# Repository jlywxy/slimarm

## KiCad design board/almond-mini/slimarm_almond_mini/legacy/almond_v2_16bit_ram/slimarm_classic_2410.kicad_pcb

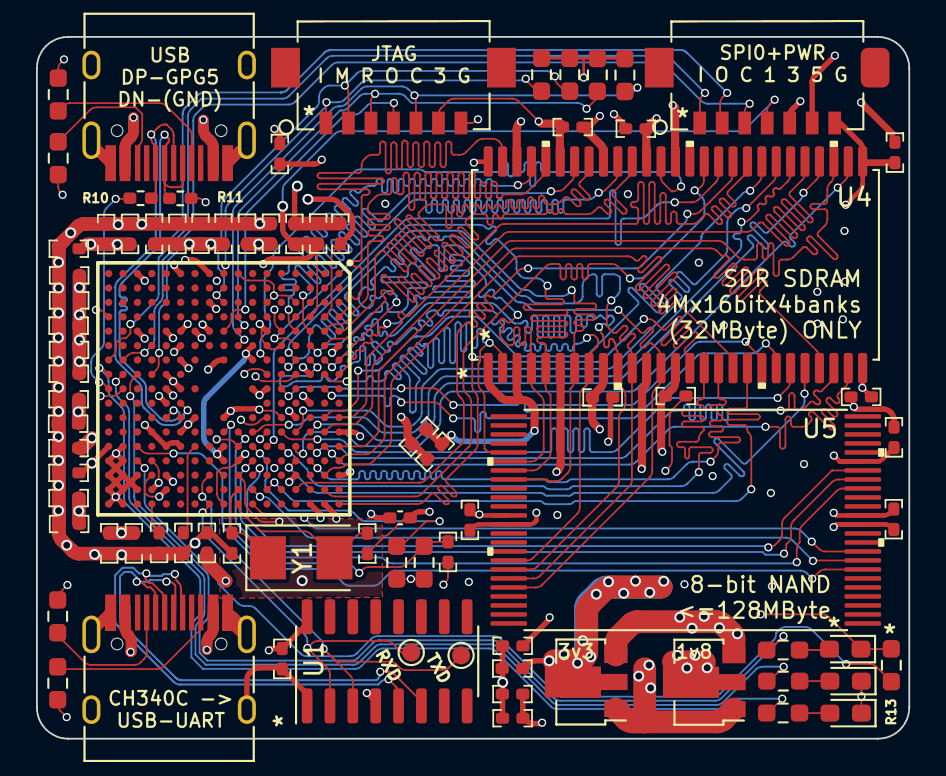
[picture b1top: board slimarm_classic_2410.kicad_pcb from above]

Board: 4 copper layers, 48.5 x 39.0 mm, 81 parts (0 on the bottom side), 81 nets.

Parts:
C1, C2: 5pF; 0402
C3, C4, C5, C7, C8, C11, C13, C14, C15, C16, C17, C18, C19, C20, C21, C22, C23, C24, C25, C26, C27, C28, C30, C31, C32, C33, C34, C35, C36, C37, C38, C39, C40, C41, C42, C43, C44, C45, C46, C47, C48, C49, C50, C51: 100nF; 0402
C6, C12: 22pF; 0402
C29: 100nF; C_0402_1005Metric_Pad0.74x0.62mm_HandSolder
D1, D2, D3: LED; LED_0603_1608Metric_Pad1.05x0.95mm_HandSolder
IC1: S3C2410AXX-YO; BGA272C80P17X17_1400X1400X116
J1, J4: USB_C_Receptacle_USB2.0; USB_C_Receptacle_HRO_TYPE-C-31-M-12
J2, J3: DF13A-7P-1.25H21
R1: 1.5k; R_0603_1608Metric_Pad0.98x0.95mm_HandSolder
R2, R14, R15, R16, R17: 10k; R_0603_1608Metric_Pad0.98x0.95mm_HandSolder
R4, R5, R6: 5.6k; R_0603_1608Metric_Pad0.98x0.95mm_HandSolder
R7, R8, R9, R12: 5.1k; R_0603_1608Metric_Pad0.98x0.95mm_HandSolder
R10, R11: NC; R_0402_1005Metric_Pad0.72x0.64mm_HandSolder
R13: 0; R_0603_1608Metric_Pad0.98x0.95mm_HandSolder
RXD: TestPoint; TestPoint_Pad_D1.0mm
TXD: TestPoint; TestPoint_Pad_D1.0mm
U1: CH340C; SOIC-16_3.9x9.9mm_P1.27mm
U4: HY57V561620FTP
U5: K9F5608U0C; M29W640FB70N6E
U6: AMS1117; SOT-89-3
U7: AMS1117-1.8; SOT-89-3
Y1: 12MHz; Crystal_SMD_5032-2Pin_5.0x3.2mm

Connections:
+1V8: C33.2, C34.2, C35.2, C36.2, C37.2, C38.2, C39.2, C40.2, C41.2, C42.2, C43.2, C44.2, C45.2, C46.2, C47.2, C49.2, IC1.C4 (VDDI_1), IC1.C8 (VDDI_2), IC1.C17 (VDDI_3), IC1.D11 (VDDI_4), IC1.G6 (VDDALIVE_1), IC1.G7 (VDDIARM_1), IC1.J13 (VDDI_5), IC1.J14 (VDDALIVE_2), IC1.K3 (VDDIARM_2), IC1.L5 (VDDIARM_3), IC1.L11 (VDDI_UPLL), IC1.M7 (VDDIARM_4), IC1.M12 (RTCVDD), IC1.N5 (VDDIARM_5), IC1.N10 (VDDIARM_6), IC1.P14 (VDDI_MPLL), IC1.P16 (XTIRTC), IC1.R1 (VDDIARM_7), J2.4, U7.2 (VO)
+3V3: C3.2, C4.2, C5.2, C7.2, C8.2, C11.2, C13.2, C14.2, C15.2, C16.2, C18.2, C19.2, C20.2, C21.2, C22.2, C23.2, C24.2, C25.2, C26.2, C27.2, C28.2, C29.2, C30.2, C31.2, C32.2, C50.2, IC1.A6 (VDDMOP_1), IC1.A15 (VDDMOP_2), IC1.B4 (VDDMOP_3), IC1.D8 (VDDMOP_4), IC1.E5 (VDDMOP_5), IC1.E11 (VDDMOP_6), IC1.H14 (VDDMOP_7), IC1.J11 (EXTCLK), IC1.J17 (NBATT_FLT), IC1.K1 (VDDOP_1), IC1.M6 (VDDOP_2), IC1.N9 (VDDOP_3), IC1.N16 (VDDOP_4), IC1.P15 (VDDA_ADC), IC1.U13 (NCON), J2.5, J3.6, R1.1, R2.2, R14.1, R15.1, R16.1, R17.1, U1.4 (V3), U1.16 (VCC), U4.1 (VDD), U4.3 (VDDQ), U4.9 (VDDQ), U4.14 (VDD), U4.27 (VDD), U4.43 (VDDQ), U4.49 (VDDQ), U5.12 (VCC), U5.19 (WP#), U5.37 (VCC), U6.2 (VO)
+5V: C17.2, C48.2, J1.A4 (VBUS), J1.A9 (VBUS), J1.B4 (VBUS), J1.B9 (VBUS), J2.6, J4.A4 (VBUS), J4.A9 (VBUS), J4.B4 (VBUS), J4.B9 (VBUS), U6.3 (VI), U7.3 (VI)
/BUS_ADR1: IC1.D14 (ADDR1), U4.23 (A0)
/BUS_ADR2: IC1.A14 (ADDR2), U4.24 (A1)
/BUS_ADR3: IC1.C13 (ADDR3), U4.25 (A2)
/BUS_ADR4: IC1.B13 (ADDR4), U4.26 (A3)
/BUS_ADR5: IC1.D13 (ADDR5), U4.29 (A4)
/BUS_ADR6: IC1.A13 (ADDR6), U4.30 (A5)
/BUS_ADR7: IC1.C12 (ADDR7), U4.31 (A6)
/BUS_ADR8: IC1.B12 (ADDR8), U4.32 (A7)
/BUS_ADR9: IC1.G12 (ADDR9), U4.33 (A8)
/BUS_ADR10: IC1.D12 (ADDR10), U4.34 (A9)
/BUS_ADR11: IC1.E12 (ADDR11), U4.22 (A10/AP)
/BUS_ADR12: IC1.B11 (ADDR12), U4.35 (A11)
/BUS_ADR13: IC1.A11 (ADDR13), U4.36 (A12)
/BUS_ADR23: IC1.E9 (ADDR23/GPA8), U4.20 (BS0)
/BUS_ADR24: IC1.B9 (ADDR24/GPA9), U4.21 (BS1)
/BUS_DAT0: IC1.B8 (DATA0), U4.2 (DQ0), U5.29 (I/O0)
/BUS_DAT1: IC1.A8 (DATA1), U4.4 (DQ1), U5.30 (I/O1)
/BUS_DAT2: IC1.D7 (DATA2), U4.5 (DQ2), U5.31 (I/O2)
/BUS_DAT3: IC1.E7 (DATA3), U4.7 (DQ3), U5.32 (I/O3)
/BUS_DAT4: IC1.C7 (DATA4), U4.8 (DQ4), U5.41 (I/O4)
/BUS_DAT5: IC1.B7 (DATA5), U4.10 (DQ5), U5.42 (I/O5)
/BUS_DAT6: IC1.A7 (DATA6), U4.11 (DQ6), U5.43 (I/O6)
/BUS_DAT7: IC1.C6 (DATA7), U4.13 (DQ7), U5.44 (I/O7)
/BUS_DAT8: IC1.F7 (DATA8), U4.42 (DQ8)
/BUS_DAT9: IC1.B6 (DATA9), U4.44 (DQ9)
/BUS_DAT10: IC1.D6 (DATA10), U4.45 (DQ10)
/BUS_DAT11: IC1.A5 (DATA11), U4.47 (DQ11)
/BUS_DAT12: IC1.C5 (DATA12), U4.48 (DQ12)
/BUS_DAT13: IC1.B5 (DATA13), U4.50 (DQ13)
/BUS_DAT14: IC1.D5 (DATA14), U4.51 (DQ14)
/BUS_DAT15: IC1.A4 (DATA15), U4.53 (DQ15)
/BUS_NWAIT: IC1.G13 (NWAIT), R1.2
/BUS_NWE: IC1.E13 (NWE), U4.16 (WE)
/CH_DN: J4.A7 (D-), J4.B7 (D-), U1.6 (UD-)
/CH_DP: J4.A6 (D+), J4.B6 (D+), U1.5 (UD+)
/DRAM_CS: IC1.F16 (NGCS6:NSCS0), U4.19 (CS)
/DRAM_DQML: IC1.A17 (NBE0:NWBE0:DQM0), U4.15 (LDQM)
/DRAM_DQMU: IC1.B16 (NBE1:NWBE1:DQM1), U4.39 (UDQM)
/DRAM_NSCAS: IC1.C14 (NSCAS), U4.17 (CAS)
/DRAM_NSRAS: IC1.B15 (NSRAS), U4.18 (RAS)
/DRAM_SCKE: IC1.D16 (SCKE), U4.37 (CKE)
/DRAM_SCLK: IC1.F13 (SCLK0), U4.38 (CLK)
/GPIO_G0: IC1.R8 (EINT8/GPG0), R5.1
/GPIO_G1: IC1.U8 (EINT9/GPG1), R6.1
/GPIO_G2: IC1.T8 (EINT10/NSS0/GPG2), R4.1
/GPIO_G5: IC1.U9 (EINT13/SPIMISO1/GPG5), R10.2
/JTAG_NTRST: IC1.H5 (NTRST), J3.3, R14.2
/JTAG_TCK: IC1.H6 (TCK), J3.5, R15.2
/JTAG_TDI: IC1.J1 (TDI), J3.1, R17.2
/JTAG_TDO: IC1.J5 (TDO), J3.4
/JTAG_TMS: IC1.J3 (TMS), J3.2, R16.2
/NAND_ALE: IC1.G14 (ALE/GPA18), U5.17 (ALE)
/NAND_CLE: IC1.H12 (CLE/GPA17), U5.16 (CLE)
/NAND_NFCE: IC1.G17 (NFCE/GPA22), U5.9 (CE#)
/NAND_NFRE: IC1.G16 (NFRE/GPA20), U5.8 (RE#)
/NAND_NFWE: IC1.G15 (NFWE/GPA19), U5.18 (WE#)
/NAND_RNB: IC1.R13 (R/NB), U5.7 (R/B#)
/NRESET: C51.1, IC1.J12 (NRESET), R2.1
/OM0: IC1.R14 (OM0), R13.2
/SPI0_CLK: IC1.P8 (SPICLK0/GPE13), J2.3
/SPI0_MISO: IC1.T7 (SPIMISO0/GPE11), J2.1
/SPI0_MOSI: IC1.U7 (SPIMOSI0/GPE12), J2.2
/UART_RX: IC1.K17 (RXD0/GPH3), RXD.1, U1.2 (TXD)
/UART_TX: IC1.K15 (TXD0/GPH2), TXD.1, U1.3 (RXD)
/USB_DN: IC1.N11 (DN1/PDN0), J1.A7 (D-), J1.B7 (D-), R11.1
/USB_DP: IC1.M10 (DP1/PDP0), J1.A6 (D+), J1.B6 (D+), R10.1
/XTAL_IN: C12.2, IC1.H17 (XTIPLL), Y1.2
/XTAL_OUT: C6.2, IC1.H16 (XTOPLL), Y1.1
GND: C1.2, C2.2, C3.1, C4.1, C5.1, C6.1, C7.1, C8.1, C11.1, C12.1, C13.1, C14.1, C15.1, C16.1, C17.1, C18.1, C19.1, C20.1, C21.1, C22.1, C23.1, C24.1, C25.1, C26.1, C27.1, C28.1, C29.1, C30.1, C31.1, C32.1, C33.1, C34.1, C35.1, C36.1, C37.1, C38.1, C39.1, C40.1, C41.1, C42.1, C43.1, C44.1, C45.1, C46.1, C47.1, C48.1, C49.1, C50.1, C51.2, D1.1 (K), D2.1 (K), D3.1 (K), IC1.A12 (VSSMOP_1), IC1.B17 (VSSI_1), IC1.C10 (VSSMOP_2), IC1.D3 (VSSMOP_3), IC1.D15 (VSSMOP_4), IC1.E6 (VSSMOP_5), IC1.F3 (VSSMOP_6), IC1.F5 (VSSOP_1), IC1.F6 (VSSI_2), IC1.F8 (VSSMOP_7), IC1.F9 (VSSI_3), IC1.F11 (VSSI_4), IC1.F12 (VSSMOP_8), IC1.G9 (VSSMOP_9), IC1.H1 (VSSIARM_1), IC1.H13 (VSSOP_2), IC1.H15 (VSSI_5), IC1.J7 (VSSIARM_2), IC1.K5 (VSSOP_3), IC1.M1 (VSSIARM_3), IC1.M5 (VSSIARM_4), IC1.M9 (VSSIARM_5), IC1.M13 (VSSI_MPLL), IC1.N8 (VSSIARM_6), IC1.N13 (AIN7), IC1.N15 (VSSI_UPLL), IC1.P12 (VSSOP_4), IC1.R5 (VSSOP_5), IC1.R15 (AIN4), IC1.R16 (AIN6), IC1.T9 (VSSOP_6), IC1.T13 (OM3), IC1.T14 (VSSA_ADC), IC1.T15 (AIN1), IC1.T16 (AIN3), IC1.T17 (AIN5), IC1.U4 (VSSIARM_7), IC1.U14 (OM2), IC1.U15 (OM1), IC1.U16 (AIN0), IC1.U17 (AIN2), J1.A1 (GND), J1.A12 (GND), J1.B1 (GND), J1.B12 (GND), J1.S1 (SHIELD), J2.7, J3.7, J4.A1 (GND), J4.A12 (GND), J4.B1 (GND), J4.B12 (GND), J4.S1 (SHIELD), R7.1, R8.1, R9.1, R11.2, R12.1, R13.1, U1.1 (GND), U4.6 (VSSQ), U4.12 (VSSQ), U4.28 (VSS), U4.41 (VSS), U4.46 (VSSQ), U4.52 (VSSQ), U4.54 (VSS), U5.13 (VSS), U5.36 (VSS), U6.1 (ADJ), U7.1 (GND)
unnamed: D1.2 (A), R4.2
unnamed: D2.2 (A), R5.2
unnamed: D3.2 (A), R6.2
unnamed: C2.1, IC1.P17 (MPLLCAP)
unnamed: C1.1, IC1.L13 (UPLLCAP)
unnamed: J1.A5 (CC1), R8.2
unnamed: J1.B5 (CC2), R9.2
unnamed: J4.A5 (CC1), R7.2
unnamed: J4.B5 (CC2), R12.2

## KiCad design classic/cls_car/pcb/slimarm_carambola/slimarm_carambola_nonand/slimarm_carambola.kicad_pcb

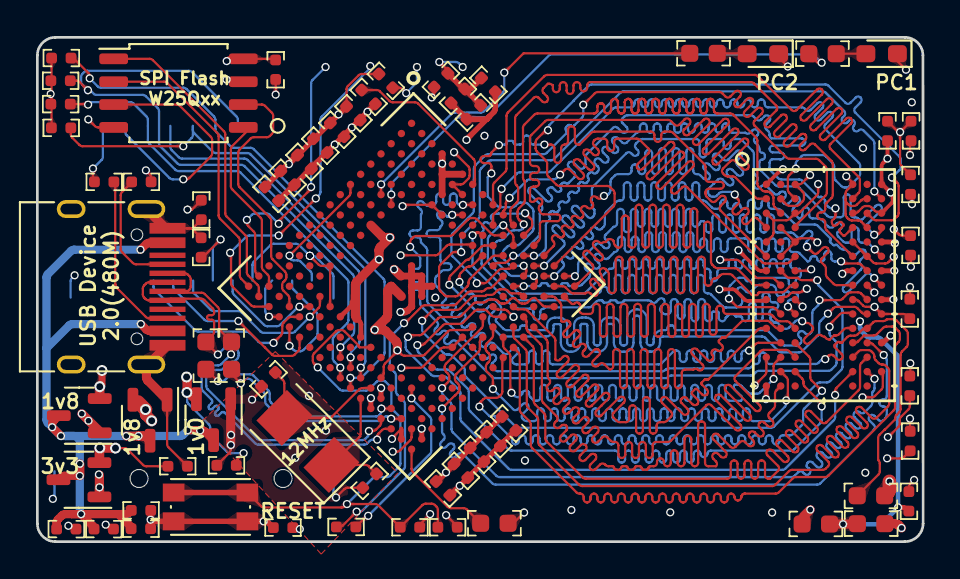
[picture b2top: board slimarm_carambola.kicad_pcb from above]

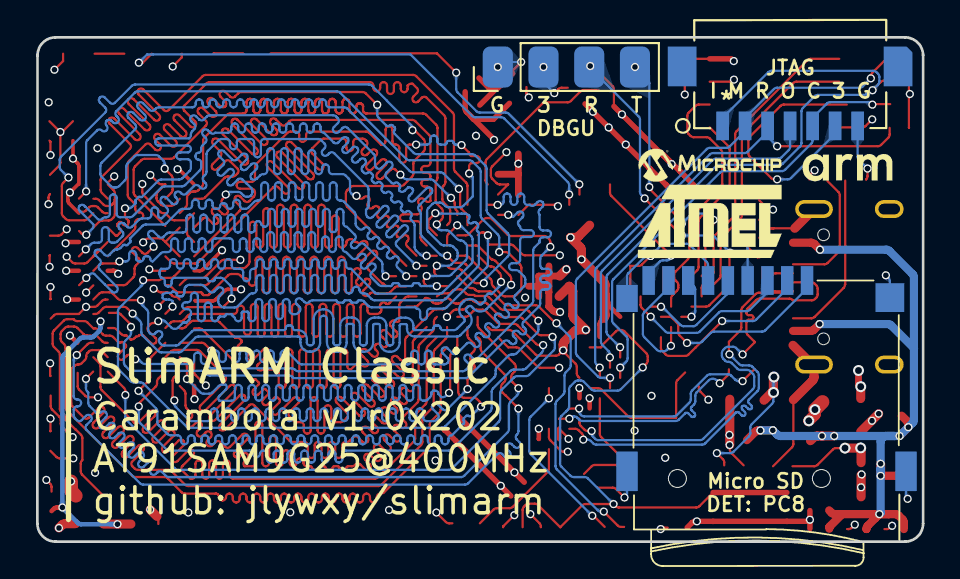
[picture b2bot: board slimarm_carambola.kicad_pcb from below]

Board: 4 copper layers, 49.2 x 28.0 mm, 69 parts (3 on the bottom side), 84 nets.

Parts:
C1, C2, C3, C4, C5, C6, C7, C8, C9, C10, C11, C12, C13, C14, C15, C16, C19, C20, C21, C22, C23, C24, C25, C27, C28: 100nF; 0402
C26, C31, C32, C33, C34, C35, C36, C37, C38, C39, C40, C41: 22pF; 0402
D1, D2: LED; LED_0603_1608Metric_Pad1.05x0.95mm_HandSolder
J1: USB_C_Receptacle_USB2.0; USB_TYPEC_Receptacle
J2: Conn_01x04; PinHeader_1x04_P2.54mm_Vertical
J4: DF13A-7P-1.25H21
R1, R2, R10, R11: 5.1k; 0402
R3: 6.8k; 0603
R5, R7: 39; 0603
R9, R13, R22, R23, R24: 10k; 0402
R12: 470k; 0603
R14, R15: 1.5k; 0603
R20, R21: 5.6k; 0603
SW1: SW_MEC_5E; BUTTON_4P_3x4
U1: AT91SAM9G25-CU; AT91SAM9G25_JKT
U2: 16bit-DDR2-8bank-FBGA84; BGA84_DDR2
U3: W25Q128JVS; SOIC-8_5.23x5.23mm_P1.27mm
U4: MicroSD-TF_PUSH-SHOUHAN
U5, U6, U7, U8: XC6206PxxxMR; SOT-23-3
Y1: Crystal; Crystal_SMD_5032-2Pin_5.0x3.2mm

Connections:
+5V: C33.2, C35.2, C37.2, C39.2, J1.A4 (VBUS), J1.A9 (VBUS), J1.B4 (VBUS), J1.B9 (VBUS), U5.3 (VI), U6.3 (VI), U7.3 (VI), U8.3 (VI)
/1v0_CPUCORE: C12.2, C13.2, C14.2, C15.2, C16.2, C40.2, U1.H14 (VDDCORE), U1.K8 (VDDCORE), U1.K9 (VDDCORE), U1.R12 (VDDPLLA), U1.T17 (VDDUTMIC), U8.2 (VO)
/1v8_CPUMEM: C9.2, C10.2, C11.2, C36.2, R10.2, U1.D10 (VDDIOM), U1.D13 (VDDIOM), U1.F14 (VDDIOM), U6.2 (VO)
/1v8_DDR: C19.2, C20.2, C21.2, C22.2, C23.2, C24.2, C25.2, C38.2, R12.2, R15.2, U2.A1 (VDD), U2.A9 (VDDQ), U2.C1 (VDDQ), U2.C3 (VDDQ), U2.C7 (VDDQ), U2.C9 (VDDQ), U2.E1 (VDD), U2.E9 (VDDQ), U2.G1 (VDDQ), U2.G3 (VDDQ), U2.G7 (VDDQ), U2.G9 (VDDQ), U2.J1 (VDD), U2.J9 (VDD), U2.M9 (VDD), U2.R1 (VDD), U7.2 (VO)
/3v3: C1.2, C2.2, C3.2, C4.2, C5.2, C6.2, C7.2, C8.2, C27.2, C28.2, C34.2, J2.2, J4.6, R9.2, R11.1, R13.2, R22.2, R23.2, R24.2, U1.A4 (ADVREF), U1.A6 (XIN32), U1.B5 (VDDBU), U1.C6 (VDDANA), U1.H4 (VDDIOP1), U1.J14 (VDDNF), U1.K14 (VDDNF), U1.P7 (VDDIOP0), U1.P9 (BMS), U1.T13 (VDDOSC), U1.U16 (VDDUTMII), U3.3 (IO2), U3.7 (IO3), U3.8 (VCC), U4.4 (VDD), U5.2 (VO)
/DDR_A0: U1.H15 (A2), U2.M8 (A0)
/DDR_A1: U1.H17 (A3), U2.M3 (A1)
/DDR_A2: U1.G17 (A4), U2.M7 (A2)
/DDR_A3: U1.G16 (A5), U2.N2 (A3)
/DDR_A4: U1.F17 (A6), U2.N8 (A4)
/DDR_A5: U1.E17 (A7), U2.N3 (A5)
/DDR_A6: U1.F16 (A8), U2.N7 (A6)
/DDR_A7: U1.G15 (A9), U2.P2 (A7)
/DDR_A8: U1.G14 (A10), U2.P8 (A8)
/DDR_A9: U1.F15 (A11), U2.P3 (A9)
/DDR_A10: U1.C8 (SDA10), U2.M2 (A10/AP)
/DDR_A11: U1.C17 (A13), U2.P7 (A11)
/DDR_A12: U1.E16 (A14), U2.R2 (A12)
/DDR_BA0: U1.C16 (A16), U2.L2 (BA0)
/DDR_BA1: U1.B17 (A17), U2.L3 (BA1)
/DDR_BA2: U1.E15 (A18), U2.L1 (BA2)
/DDR_CAS: U1.C10 (CAS), U2.L7 (CAS*)
/DDR_CKE: U1.B12 (SDCKE), U2.K2 (DKE)
/DDR_CLKN: U1.C11 (*SDCK), U2.K8 (CK*)
/DDR_CLKP: U1.D11 (SDCK), U2.J8 (CK)
/DDR_CS: R12.1, U1.B8 (NCS1), U2.L8 (CS*)
/DDR_D0: U1.D14 (D0), U2.G8 (DQ0)
/DDR_D1: U1.D15 (D1), U2.G2 (DQ1)
/DDR_D2: U1.A16 (D2), U2.H7 (DQ2)
/DDR_D3: U1.B16 (D3), U2.H3 (DQ3)
/DDR_D4: U1.A17 (D4), U2.H1 (DQ4)
/DDR_D5: U1.B15 (D5), U2.H9 (DQ5)
/DDR_D6: U1.C14 (D6), U2.F1 (DQ6)
/DDR_D7: U1.B14 (D7), U2.F9 (DQ7)
/DDR_D8: U1.A15 (D8), U2.C8 (DQ8)
/DDR_D9: U1.C15 (D9), U2.C2 (DQ9)
/DDR_D10: U1.D12 (D10), U2.D7 (DQ10)
/DDR_D11: U1.C13 (D11), U2.D3 (DQ11)
/DDR_D12: U1.A14 (D12), U2.D1 (DQ12)
/DDR_D13: U1.B13 (D13), U2.D9 (DQ13)
/DDR_D14: U1.A13 (D14), U2.B1 (DQ14)
/DDR_D15: U1.C12 (D15), U2.B9 (DQ15)
/DDR_DQM0: U1.A10 (DQM0), U2.F3 (LDM)
/DDR_DQM1: U1.B10 (DQM1), U2.B3 (UDM)
/DDR_DQS0: U1.A11 (DQS0), U2.F7 (LDQS)
/DDR_DQS1: U1.A9 (DQS1), U2.B7 (UDQS)
/DDR_RAS: U1.B11 (RAS), U2.K7 (RAS*)
/DDR_WE: U1.A12 (SDWE), U2.K3 (WE*)
/DEBUG_RXD: J2.3, U1.U3 (PA9)
/DEBUG_TXD: J2.4, U1.T1 (PA10)
/DN: J1.A7 (D-), J1.B7 (D-), R7.2, U1.U15 (HHSDMA)
/DP: J1.A6 (D+), J1.B6 (D+), R5.2, U1.U14 (HHSDPA)
/JTAG_RST: J4.3, R23.1, U1.T11 (NTRST)
/JTAG_TCK: J4.5, R24.1, U1.U10 (TCK)
/JTAG_TDI: J4.1, R13.1, U1.T9 (TDI)
/JTAG_TDO: J4.4, U1.T10 (TDO)
/JTAG_TMS: J4.2, R22.1, U1.U11 (TMS)
/MCI0_CDA: U1.P5 (PA16), U4.3 (CMD)
/MCI0_CK: U1.R5 (PA17), U4.5 (CLK)
/MCI0_DA0: U1.U4 (PA15), U4.7 (DAT0)
/MCI0_DA1: U1.U5 (PA18), U4.8 (DAT1)
/MCI0_DA2: U1.T5 (PA19), U4.1 (DAT2)
/MCI0_DA3: U1.U6 (PA20), U4.2 (CD/DAT3)
/SD_DET: U1.G1 (PC8), U4.CD
/SPI_CLK: U1.T4 (PA13), U3.6 (CLK)
/SPI_CS: U1.U2 (PA14), U3.1 (~CS)
/SPI_MISO: U1.U1 (PA11), U3.2 (DO(IO1))
/SPI_MOSI: U1.T2 (PA12), U3.5 (DI(IO0))
/USBD_FS_DN: R7.1, U1.T15 (HFSDMA)
/USBD_FS_DP: R5.1, U1.T14 (HFSDPA)
/XTAL_IN: C32.1, U1.T12 (XIN), Y1.2
/XTAL_OUT: C31.2, U1.U12 (XOUT), Y1.1
GND: C1.1, C2.1, C3.1, C4.1, C5.1, C6.1, C7.1, C8.1, C9.1, C10.1, C11.1, C12.1, C13.1, C14.1, C15.1, C16.1, C19.1, C20.1, C21.1, C22.1, C23.1, C24.1, C25.1, C26.1, C27.1, C28.1, C31.1, C32.2, C33.1, C34.1, C35.1, C36.1, C37.1, C38.1, C39.1, C40.1, C41.1, D1.1 (K), D2.1 (K), J1.A1 (GND), J1.A12 (GND), J1.B1 (GND), J1.B12 (GND), J1.S1 (SHIELD), J2.1, J4.7, R1.2, R2.2, R3.1, R14.1, SW1.1, SW1.2, U1.B6 (GNDBU), U1.B7 (TST), U1.D6 (GNDANA), U1.D7 (JTAGSEL), U1.H8 (GNDCORE), U1.H9 (GNDIOM), U1.H10 (GNDIOM), U1.J8 (GNDCORE), U1.J9 (GNDIOM), U1.J10 (GNDIOM), U1.K10 (GNDCORE), U1.M4 (GNDIOP), U1.P6 (GNDIOP), U1.T16 (GNDUTMI), U1.U13 (GNDOSC), U2.A3 (VSS), U2.A7 (VSSQ), U2.B2 (VSSQ), U2.B8 (VSSQ), U2.D2 (VSSQ), U2.D8 (VSSQ), U2.E3 (VSS), U2.E7 (VSSQ), U2.F2 (VSSQ), U2.F8 (VSSQ), U2.H2 (VSSQ), U2.H8 (VSSQ), U2.J3 (VSS), U2.J7 (VSS), U2.K9 (ODT), U2.N1 (VSS), U2.P9 (VSS), U3.4 (GND), U4.0 (SHIELD), U4.6 (VSS), U5.1 (GND), U6.1 (GND), U7.1 (GND), U8.1 (GND)
unnamed: D1.2 (A), R20.1
unnamed: D2.2 (A), R21.1
unnamed: J1.A5 (CC1), R1.1
unnamed: J1.B5 (CC2), R2.1
unnamed: C41.2, R11.2, SW1.3 (K), SW1.4 (A), U1.P10 (NRST)
unnamed: R20.2, U1.F4 (PC1)
unnamed: R21.2, U1.F3 (PC2)
unnamed: R9.1, U1.A7 (WKUP)
unnamed: R10.1, U1.P14 (PD5)
unnamed: R3.2, U1.U17 (VBG)
unnamed: C26.2, R14.2, R15.1, U2.J2 (VREF)

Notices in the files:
parts and their libraries:
Copyright 2021 Accelerated Designs. All rights reserved.
